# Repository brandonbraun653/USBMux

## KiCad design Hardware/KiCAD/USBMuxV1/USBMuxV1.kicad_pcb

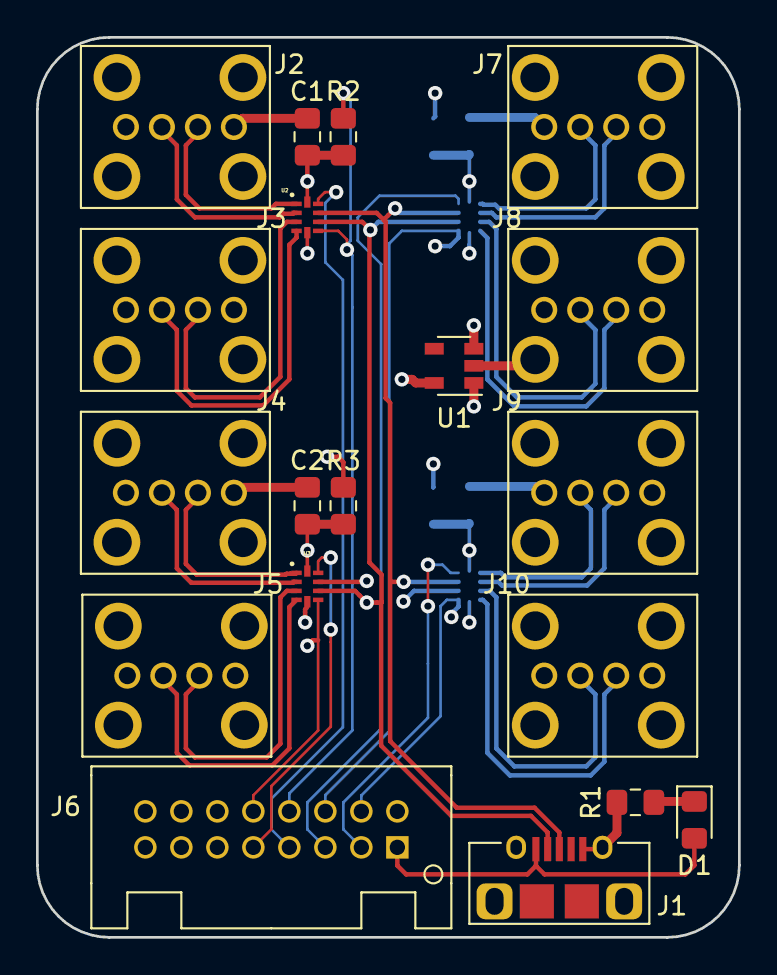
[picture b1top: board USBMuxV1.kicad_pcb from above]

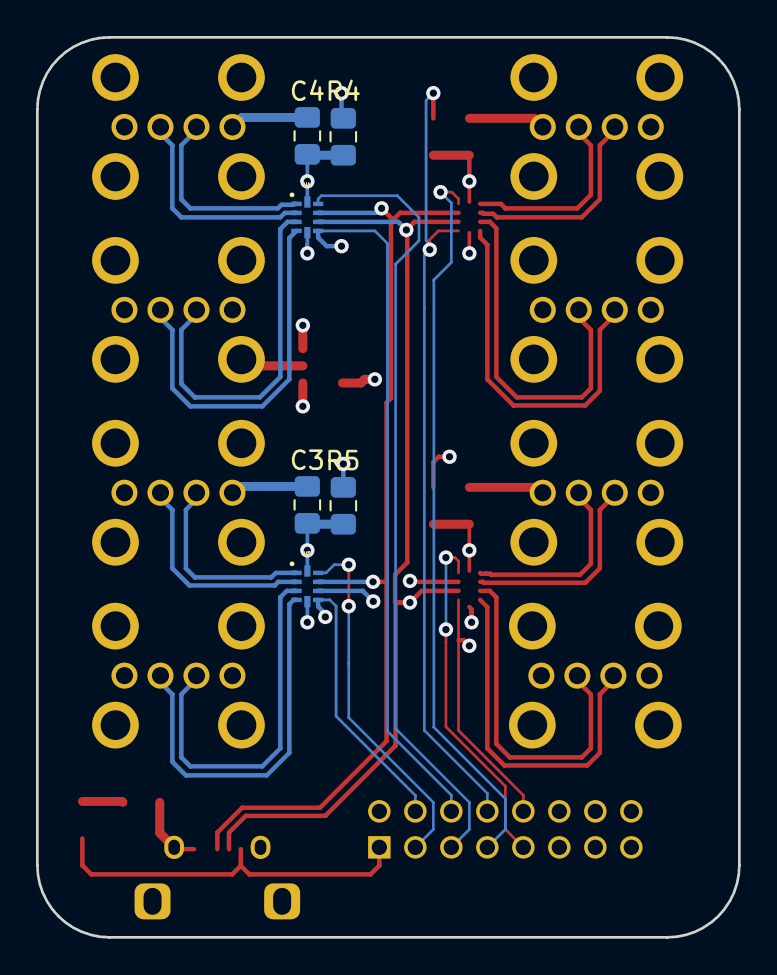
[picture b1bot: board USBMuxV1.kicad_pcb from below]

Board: 4 copper layers, 39.0 x 50.0 mm, 25 parts (6 on the bottom side), 30 nets.

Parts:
C1, C2, C3, C4: 100nF; C_0805_2012Metric_Pad1.15x1.40mm_HandSolder
D1: PWR GOOD; LED_0805_2012Metric_Pad1.15x1.40mm_HandSolder
J1: USB_B_Micro; Amphenol-MicroB
J2, J3, J4, J5, J7, J8, J9, J10: USB_A; KUSBXHT-SLAS1N-O-HRF
J6: DF51K-16DP-XXXX; DF51K-16DP-2SA
R1: 500; R_0805_2012Metric_Pad1.15x1.40mm_HandSolder
R2, R3, R4, R5: 10k; R_0805_2012Metric_Pad1.15x1.40mm_HandSolder
U1: TLV71333PDBV; SOT-23-5
U2, U3, U4, U5: TS3USB221A; QFN-10-RSE

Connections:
+3V3: C1.1, C2.1, C3.1, C4.1, R2.1, R3.1, R4.1, R5.1, U1.5, U2.10, U3.10, U4.10, U5.10
+5V: D1.2, J1.1, J2.1, J3.1, J4.1, J5.1, J6.1, J7.1, J8.1, J9.1, J10.1, U1.1, U1.3
Bank1OE: J6.14, R4.2, U4.6
Bank1Switch: J6.3, U4.9
Bank2OE: J6.15, R5.2, U5.6
Bank2Switch: J6.2, U5.9
Bank3OE: J6.13, R2.2, U2.6
Bank3Switch: J6.4, U2.9
Bank4OE: J6.12, R3.2, U3.6
Bank4Switch: J6.5, U3.9
GND: C1.2, C2.2, C3.2, C4.2, J1.5, J2.4, J2.5, J3.4, J3.5, J4.4, J4.5, J5.4, J5.5, J6.8, J6.9, J6.16, J7.4, J7.5, J8.4, J8.5, J9.4, J9.5, J10.4, J10.5, R1.1, U1.2, U2.5, U3.5, U4.5, U5.5
GlobalD+: J1.3, U2.8, U3.8, U4.8, U5.8
GlobalD-: J1.2, U2.7, U3.7, U4.7, U5.7
unnamed: D1.1, R1.2
unnamed: J2.2, U2.2
unnamed: J2.3, U2.1
unnamed: J3.2, U2.4
unnamed: J3.3, U2.3
unnamed: J4.2, U3.2
unnamed: J4.3, U3.1
unnamed: J5.2, U3.4
unnamed: J5.3, U3.3
unnamed: J7.2, U4.2
unnamed: J7.3, U4.1
unnamed: J8.2, U4.4
unnamed: J8.3, U4.3
unnamed: J9.2, U5.2
unnamed: J9.3, U5.1
unnamed: J10.2, U5.4
unnamed: J10.3, U5.3

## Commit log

2020-02-14 Initial commit. Nearly done with PCB routing.
2020-02-16 Finish routing
2020-03-22 Update the PCB for round 1 of production
